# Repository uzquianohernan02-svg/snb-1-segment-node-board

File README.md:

# SNB-1 Segment Node Board

24 V Class 2 input -> 12 V / 6 A output (TI LM5116 synchronous buck), with an optional RS-485 pixel-data
receiver (TI THVD1450) for the first node of each WS2815 run.

**Status: Rev B prototype, ready for a first prototype order.** Not yet built or bench-tested. KiCad 10 ERC and
DRC (all severities, schematic parity, zones refilled) report 0 errors / 0 warnings; reports in
`pcb/kicad/snb-erc.json` and `snb-drc.json`. Not UL-listed.

System context: the SNB-1 is the specified per-segment converter and RS-485 receiver of the LED system
Engineering Specification Rev 5 (Final, 2026-11-17), one board per 2.5 A Class 2 segment, 4 per 10 A run (1 x node1,
3 x node2-4). Before first installation the spec requires 5 prototypes to pass the bench tests in the design PDF
Sec. 10 (hold point H2).

Rev B (2026-11-17): added R16, a 2.2 Ohm HO gate resistor at Q2, to damp the long gate-drive trace. Also added
manufacturing outputs in `pcb/fab/`.

- `pcb/kicad/` - KiCad project (KiCad 10; the board is saved with filled zones). `snb.kicad_dru` holds one
  custom rule: 0.2 mm clearance at the LM5116 0.65 mm-pitch pads (Power netclass is 0.3 mm elsewhere).
- `pcb/kicad/snb_bom.csv` - bill of materials (node-variant column)
- `pcb/fab/` - manufacturing package: `snb-gerbers.zip` (Gerber X2 + Excellon, origin at the bottom-left board
  corner), pick-and-place and assembly BOM per variant (`node1` = with RS-485 receiver, `node2-4` = power only),
  `snb.step` for the enclosure fit check, `snb-top.png` render.
  Order: 125 x 85 mm, 2 layers, 1.6 mm FR-4, **2 oz copper**, HASL lead-free or ENIG.
- `SNB-1_Segment_Node_Board_Design.pdf` - calculations, schematic, layout, BOM, verification and test plan
- `pcb/design/` - generators. `netlist.py` is the single source of truth; run `sh pcb/design/build.sh`
  (needs Python 3 + numpy + reportlab, and KiCad 10 for the kicad-cli ERC/DRC and fab-export steps) to
  regenerate the schematic, routed PCB, checks, manufacturing files and PDF.
  Do not hand-edit the generated `.kicad_*` files.

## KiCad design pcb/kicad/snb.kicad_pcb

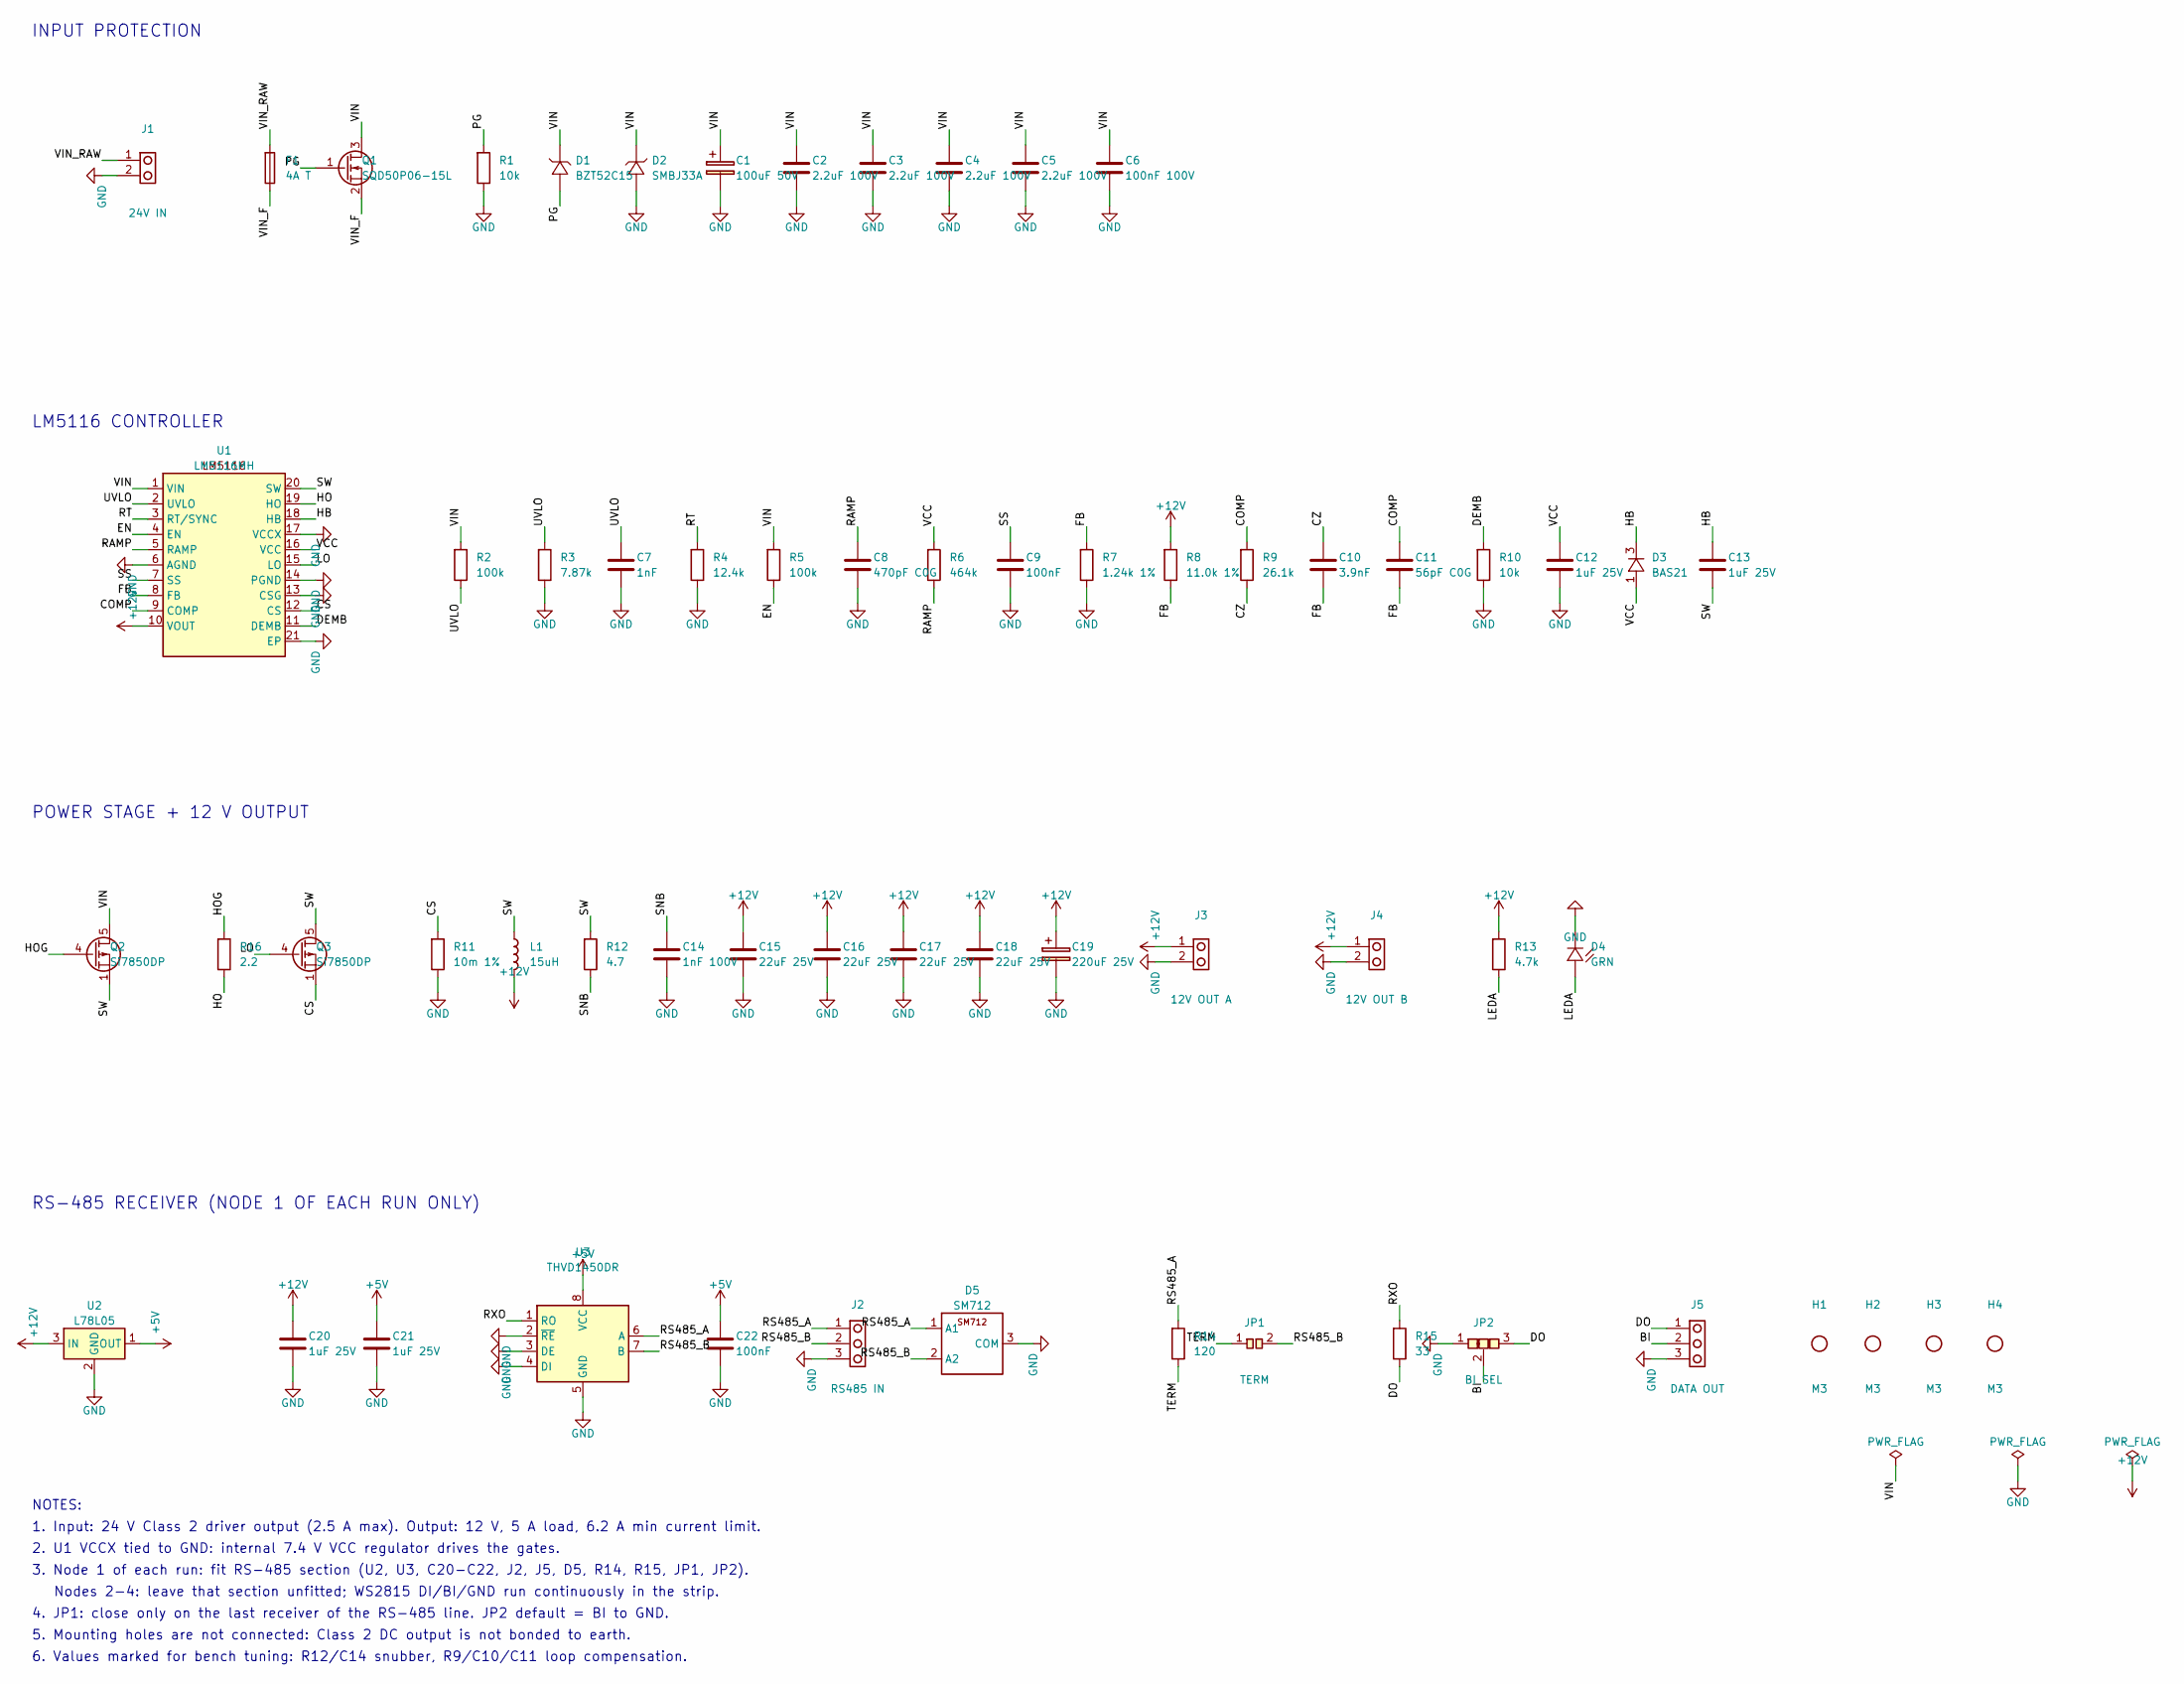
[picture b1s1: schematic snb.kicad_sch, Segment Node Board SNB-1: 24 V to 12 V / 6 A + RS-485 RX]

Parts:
C1: 100uF 50V; CP_Radial_D10.0mm_P5.00mm; MPN Panasonic EEU-FR1H101
C2, C3, C4, C5: 2.2uF 100V; C_1812_4532Metric; MPN TDK C4532X7R2A225M
C6: 100nF 100V; C_0805_2012Metric; MPN TDK C2012X7R2A104M
C7: 1nF; C_0603_1608Metric
C8: 470pF C0G; C_0603_1608Metric
C9, C22: 100nF; C_0603_1608Metric
C10: 3.9nF; C_0603_1608Metric
C11: 56pF C0G; C_0603_1608Metric
C12, C13: 1uF 25V; C_0805_2012Metric; MPN TDK C2012X7R1E105K
C14: 1nF 100V; C_0805_2012Metric
C15, C16, C17, C18: 22uF 25V; C_1210_3225Metric; MPN Murata GRM32ER71E226KE15
C19: 220uF 25V; CP_Radial_D8.0mm_P3.50mm; MPN Panasonic 25SVPF220M (OS-CON) or equiv.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
C20, C21: 1uF 25V; C_0805_2012Metric
D1: BZT52C15; D_SOD-123; MPN Nexperia BZT52C15
D2: SMBJ33A; D_SMB; MPN Littelfuse SMBJ33A
D3: BAS21; SOT-23; MPN Nexperia BAS21
D4: GRN; LED_0805_2012Metric
D5: SM712; SOT-23; MPN Semtech SM712.TCT
F1: 4A T; Fuseholder_Cylinder-5x20mm_Schurter_0031_8201_Horizontal_Op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; MPN Schurter 0031.8201 holder + 4 A time-la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
H1, H2, H3, H4: M3; MountingHole_3.2mm_M3
J1: 24V IN; TerminalBlock_Phoenix_MKDS-3-2-5.08_1x02_P5.08mm_Horizontal; MPN Phoenix 1711026 (MKDS 3/2-5,08)
J2: RS485 IN; TerminalBlock_Phoenix_MKDS-1,5-3-5.08_1x03_P5.08mm_Horizont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; MPN Phoenix 1715734
J3: 12V OUT A; TerminalBlock_Phoenix_MKDS-3-2-5.08_1x02_P5.08mm_Horizontal; MPN Phoenix 1711026
J4: 12V OUT B; TerminalBlock_Phoenix_MKDS-3-2-5.08_1x02_P5.08mm_Horizontal; MPN Phoenix 1711026
J5: DATA OUT; TerminalBlock_Phoenix_MKDS-1,5-3-5.08_1x03_P5.08mm_Horizont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; MPN Phoenix 1715734
JP1: TERM; SolderJumper-2_P1.3mm_Open_RoundedPad1.0x1.5mm
JP2: BI SEL; SolderJumper-3_P1.3mm_Open_RoundedPad1.0x1.5mm
L1: 15uH; L_Coilcraft_XAL1010-XXX; MPN Coilcraft XAL1010-153ME
Q1: SQD50P06-15L; TO-252-2; MPN Vishay SQD50P06-15L
Q2, Q3: Si7850DP; PowerPAK_SO-8_Single; MPN Vishay Si7850DP
R1: 10k; R_0805_2012Metric
R2, R5: 100k; R_0603_1608Metric
R3: 7.87k; R_0603_1608Metric
R4: 12.4k; R_0603_1608Metric
R6: 464k; R_0603_1608Metric
R7: 1.24k 1%; R_0603_1608Metric
R8: 11.0k 1%; R_0603_1608Metric
R9: 26.1k; R_0603_1608Metric
R10: 10k; R_0603_1608Metric
R11: 10m 1%; R_2010_5025Metric; MPN IRC LRC-LRF2010-01-R010-F
R12: 4.7; R_1206_3216Metric
R13: 4.7k; R_0805_2012Metric
R14: 120; R_0805_2012Metric
R15: 33; R_0603_1608Metric
R16: 2.2; R_0603_1608Metric
U1: LM5116MH; HTSSOP-20-1EP_4.4x6.5mm_P0.65mm_EP2.85x4mm; MPN TI LM5116MHX/NOPB
U2: L78L05; SOT-89-3; MPN ST L78L05ABUTR
U3: THVD1450DR; SOIC-8_3.9x4.9mm_P1.27mm; MPN TI THVD1450DR (SOIC-8)

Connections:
+5V: C21.1, C22.1, U2.1 (OUT), U3.8 (VCC)
+12V: C15.1, C16.1, C17.1, C18.1, C19.1, C20.1, J3.1, J4.1, L1.2, R8.1, R13.1, U1.10 (VOUT), U2.3 (IN)
/BI: J5.2, JP2.2 (C)
/COMP: C11.1, R9.1, U1.9 (COMP)
/CS: Q3.1 (S), Q3.2 (S), Q3.3 (S), R11.1, U1.12 (CS)
/CZ: C10.1, R9.2
/DEMB: R10.1, U1.11 (DEMB)
/DO: J5.1, JP2.3 (B), R15.2
/EN: R5.2, U1.4 (EN)
/FB: C10.2, C11.2, R7.1, R8.2, U1.8 (FB)
/HB: C13.1, D3.3 (K), U1.18 (HB)
/HO: R16.2, U1.19 (HO)
/HOG: Q2.4 (G), R16.1
/LEDA: D4.2 (A), R13.2
/LO: Q3.4 (G), U1.15 (LO)
/PG: D1.2 (A), Q1.1 (G), R1.1
/RAMP: C8.1, R6.2, U1.5 (RAMP)
/RS485_A: D5.1 (A1), J2.1, R14.1, U3.6 (A)
/RS485_B: D5.2 (A2), J2.2, JP1.2 (B), U3.7 (B)
/RT: R4.1, U1.3 (RT/SYNC)
/RXO: R15.1, U3.1 (RO)
/SNB: C14.1, R12.2
/SS: C9.1, U1.7 (SS)
/SW: C13.2, L1.1, Q2.1 (S), Q2.2 (S), Q2.3 (S), Q3.5 (D), R12.1, U1.20 (SW)
/TERM: JP1.1 (A), R14.2
/UVLO: C7.1, R2.2, R3.1, U1.2 (UVLO)
/VCC: C12.1, D3.1 (A), R6.1, U1.16 (VCC)
/VIN: C1.1, C2.1, C3.1, C4.1, C5.1, C6.1, D1.1 (K), D2.1 (K), Q1.3 (S), Q2.5 (D), R2.1, R5.1, U1.1 (VIN)
/VIN_F: F1.2, Q1.2 (D)
/VIN_RAW: F1.1, J1.1
GND: C1.2, C2.2, C3.2, C4.2, C5.2, C6.2, C7.2, C8.2, C9.2, C12.2, C14.2, C15.2, C16.2, C17.2, C18.2, C19.2, C20.2, C21.2, C22.2, D2.2 (A), D4.1 (K), D5.3 (COM), J1.2, J2.3, J3.2, J4.2, J5.3, JP2.1 (A), R1.2, R3.2, R4.2, R7.2, R10.2, R11.2, U1.6 (AGND), U1.13 (CSG), U1.14 (PGND), U1.17 (VCCX), U1.21 (EP), U2.2 (GND), U3.2 (~RE), U3.3 (DE), U3.4 (DI), U3.5 (GND)

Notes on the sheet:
INPUT PROTECTION
LM5116 CONTROLLER
POWER STAGE + 12 V OUTPUT
RS-485 RECEIVER (NODE 1 OF EACH RUN ONLY)
NOTES:
1. Input: 24 V Class 2 driver output (2.5 A max). Output: 12 V, 5 A load, 6.2 A min current limit.
2. U1 VCCX tied to GND: internal 7.4 V VCC regulator drives the gates.
3. Node 1 of each run: fit RS-485 section (U2, U3, C20-C22, J2, J5, D5, R14, R15, JP1, JP2).
Nodes 2-4: leave that section unfitted; WS2815 DI/BI/GND run continuously in the strip.
4. JP1: close only on the last receiver of the RS-485 line. JP2 default = BI to GND.
5. Mounting holes are not connected: Class 2 DC output is not bonded to earth.
6. Values marked for bench tuning: R12/C14 snubber, R9/C10/C11 loop compensation.

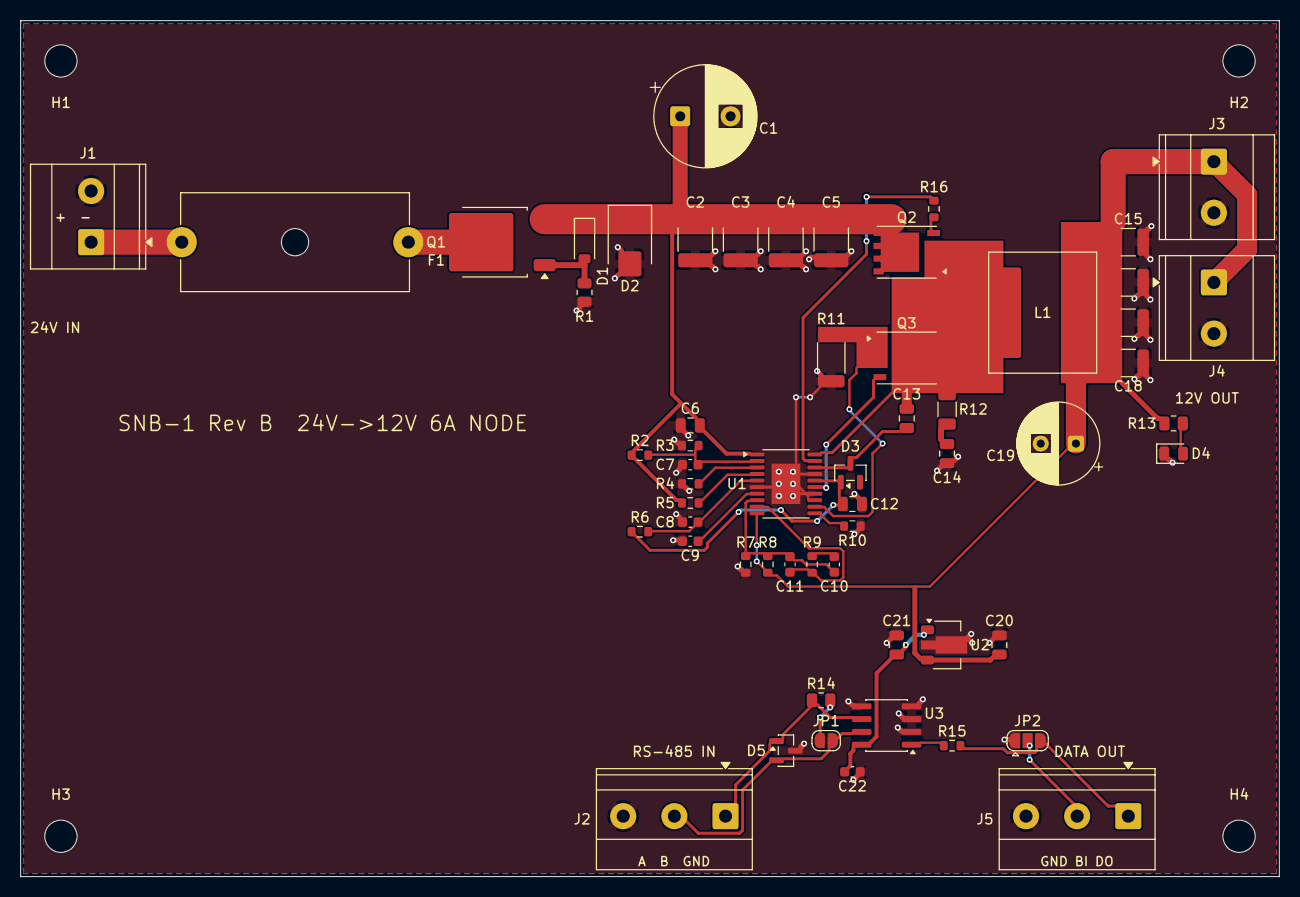
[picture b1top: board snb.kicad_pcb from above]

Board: 2 copper layers, 125.0 x 85.0 mm, 62 parts (0 on the bottom side), 31 nets.

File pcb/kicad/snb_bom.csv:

Qty,References,Value,Footprint,Manufacturer part (or equivalent),Fitted,Function
1,C1,100uF 50V,CP_Radial_D10.0mm_P5.00mm,Panasonic EEU-FR1H101,All nodes,"Bulk input, damps cable-inductance ringing on hot-plug"
4,C2 C3 C4 C5,2.2uF 100V,C_1812_4532Metric,TDK C4532X7R2A225M,All nodes,Input ceramic X7R
1,C6,100nF 100V,C_0805_2012Metric,TDK C2012X7R2A104M,All nodes,VIN pin bypass
1,C7,1nF,C_0603_1608Metric,"Any 0603 X7R ceramic, 50 V min",All nodes,UVLO filter
1,C8,470pF C0G,C_0603_1608Metric,"Any 0603 C0G ceramic, 50 V min",All nodes,"CRAMP, C0G 5%"
1,C9,100nF,C_0603_1608Metric,"Any 0603 X7R ceramic, 50 V min",All nodes,Soft start ~12 ms
1,C10,3.9nF,C_0603_1608Metric,"Any 0603 X7R ceramic, 50 V min",All nodes,CCOMP (zero ~1.6 kHz)
1,C11,56pF C0G,C_0603_1608Metric,"Any 0603 C0G ceramic, 50 V min",All nodes,CHF
1,C12,1uF 25V,C_0805_2012Metric,TDK C2012X7R1E105K,All nodes,VCC decoupling
1,C13,1uF 25V,C_0805_2012Metric,TDK C2012X7R1E105K,All nodes,Bootstrap capacitor
1,C14,1nF 100V,C_0805_2012Metric,"Any 0805 X7R ceramic, 100 V min",All nodes,Snubber C (tune on bench)
4,C15 C16 C17 C18,22uF 25V,C_1210_3225Metric,Murata GRM32ER71E226KE15,All nodes,Output ceramic X7R
1,C19,220uF 25V,CP_Radial_D8.0mm_P3.50mm,Panasonic 25SVPF220M (OS-CON) or equiv. polymer,All nodes,"Output bulk polymer, ESR ~20 mOhm"
1,C20,1uF 25V,C_0805_2012Metric,"Any 0805 X7R ceramic, 25 V min",Node 1 only,LDO input
1,C21,1uF 25V,C_0805_2012Metric,"Any 0805 X7R ceramic, 25 V min",Node 1 only,LDO output
1,C22,100nF,C_0603_1608Metric,"Any 0603 X7R ceramic, 50 V min",Node 1 only,U3 decoupling
1,D1,BZT52C15,D_SOD-123,Nexperia BZT52C15,All nodes,"15 V gate-source clamp (K=VIN, A=gate)"
1,D2,SMBJ33A,D_SMB,Littelfuse SMBJ33A,All nodes,"TVS 33 V standoff, ~53 V clamp (FETs rated 60 V)"
1,D3,BAS21,SOT-23,Nexperia BAS21,All nodes,Bootstrap diode 250 V
1,D4,GRN,LED_0805_2012Metric,Any 0805 green LED (2 mA),All nodes,12 V present
1,D5,SM712,SOT-23,Semtech SM712.TCT,Node 1 only,RS-485 line TVS
1,F1,4A T,Fuseholder_Cylinder-5x20mm_Schurter_0031_8201_Horizontal_Open,"Schurter 0031.8201 holder + 4 A time-lag 5x20 fuse, DC-rated >= 32 V",All nodes,Field-replaceable 4 A time-delay fuse (Spec Rev 5 item 10)
4,H1 H2 H3 H4,M3,MountingHole_3.2mm_M3,MountingHole_3.2mm_M3,Not a part (hole),"Mounting hole, not bonded (Class 2 output not earthed)"
1,J1,24V IN,TerminalBlock_Phoenix_MKDS-3-2-5.08_1x02_P5.08mm_Horizontal,"Phoenix 1711026 (MKDS 3/2-5,08)",All nodes,"Terminal block 2p 5.08 mm, 24-12 AWG, 24 A"
1,J2,RS485 IN,"TerminalBlock_Phoenix_MKDS-1,5-3-5.08_1x03_P5.08mm_Horizontal",Phoenix 1715734,Node 1 only,Twisted-pair data from controller TX
1,J3,12V OUT A,TerminalBlock_Phoenix_MKDS-3-2-5.08_1x02_P5.08mm_Horizontal,Phoenix 1711026,All nodes,12 V to strip injection (start)
1,J4,12V OUT B,TerminalBlock_Phoenix_MKDS-3-2-5.08_1x02_P5.08mm_Horizontal,Phoenix 1711026,All nodes,12 V to strip injection (mid/end)
1,J5,DATA OUT,"TerminalBlock_Phoenix_MKDS-1,5-3-5.08_1x03_P5.08mm_Horizontal",Phoenix 1715734,Node 1 only,To strip DI / BI / GND
1,JP1,TERM,SolderJumper-2_P1.3mm_Open_RoundedPad1.0x1.5mm,SolderJumper-2_P1.3mm_Open_RoundedPad1.0x1.5mm,Node 1 only,Close to terminate (end of line)
1,JP2,BI SEL,SolderJumper-3_P1.3mm_Open_RoundedPad1.0x1.5mm,SolderJumper-3_P1.3mm_Open_RoundedPad1.0x1.5mm,Node 1 only,Bridge 1-2 at assembly: BI = GND (default); 2-3: BI = DI
1,L1,15uH,L_Coilcraft_XAL1010-XXX,Coilcraft XAL1010-153ME,All nodes,"15 uH, Isat >= 13 A, shielded"
1,Q1,SQD50P06-15L,TO-252-2,Vishay SQD50P06-15L,All nodes,"P-MOSFET -60 V, reverse-polarity protection"
1,Q2,Si7850DP,PowerPAK_SO-8_Single,Vishay Si7850DP,All nodes,High-side N-MOSFET 60 V
1,Q3,Si7850DP,PowerPAK_SO-8_Single,Vishay Si7850DP,All nodes,Low-side N-MOSFET 60 V
1,R1,10k,R_0805_2012Metric,"Any 0805 thick-film resistor, 1 %, 100 ppm/C",All nodes,P-FET gate pull-down
1,R2,100k,R_0603_1608Metric,"Any 0603 thick-film resistor, 1 %, 100 ppm/C",All nodes,UVLO top (RUV2 > 500 x 60 V)
1,R3,7.87k,R_0603_1608Metric,"Any 0603 thick-film resistor, 1 %, 100 ppm/C",All nodes,UVLO bottom: shutdown at ~16 V
1,R4,12.4k,R_0603_1608Metric,"Any 0603 thick-film resistor, 1 %, 100 ppm/C",All nodes,RT: 250 kHz
1,R5,100k,R_0603_1608Metric,"Any 0603 thick-film resistor, 1 %, 100 ppm/C",All nodes,EN pull-up to VIN (EN rated 100 V)
1,R6,464k,R_0603_1608Metric,"Any 0603 thick-film resistor, 1 %, 100 ppm/C",All nodes,RRAMP to VCC (VOUT > 7.5 V slope comp)
1,R7,1.24k 1%,R_0603_1608Metric,"Any 0603 thick-film resistor, 1 %, 100 ppm/C",All nodes,RFB1
1,R8,11.0k 1%,R_0603_1608Metric,"Any 0603 thick-film resistor, 1 %, 100 ppm/C",All nodes,RFB2 -> VOUT = 11.99 V
1,R9,26.1k,R_0603_1608Metric,"Any 0603 thick-film resistor, 1 %, 100 ppm/C",All nodes,RCOMP
1,R10,10k,R_0603_1608Metric,"Any 0603 thick-film resistor, 1 %, 100 ppm/C",All nodes,RDEMB: fully synchronous after soft start
1,R11,10m 1%,R_2010_5025Metric,IRC LRC-LRF2010-01-R010-F,All nodes,Current sense RS: limit 6.2 A min / 7.8 A typ
1,R12,4.7,R_1206_3216Metric,"Any 1206 thick-film resistor, 1 %, 100 ppm/C",All nodes,Snubber R (tune on bench)
1,R13,4.7k,R_0805_2012Metric,"Any 0805 thick-film resistor, 1 %, 100 ppm/C",All nodes,LED resistor (~2 mA)
1,R14,120,R_0805_2012Metric,"Any 0805 thick-film resistor, 1 %, 100 ppm/C",Node 1 only,Line termination
1,R15,33,R_0603_1608Metric,"Any 0603 thick-film resistor, 1 %, 100 ppm/C",Node 1 only,Data series resistor
1,R16,2.2,R_0603_1608Metric,"Any 0603 thick-film resistor, 1 %, 100 ppm/C",All nodes,"HO gate resistor at Q2 (damps long gate trace; 0-4.7 Ohm, tune on bench)"
1,U1,LM5116MH,HTSSOP-20-1EP_4.4x6.5mm_P0.65mm_EP2.85x4mm,TI LM5116MHX/NOPB,All nodes,"Synchronous buck controller, 6-100 V"
1,U2,L78L05,SOT-89-3,ST L78L05ABUTR,Node 1 only,5 V LDO for receiver
1,U3,THVD1450DR,SOIC-8_3.9x4.9mm_P1.27mm,TI THVD1450DR (SOIC-8),Node 1 only,"RS-485 transceiver 50 Mbps, receive-only"
